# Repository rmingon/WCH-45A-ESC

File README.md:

# WCH-45A-ESC

An open-hardware 45A Electronic Speed Controller (ESC) project based on the WCH CH32M007 RISC-V microcontroller.

## Project Overview

This project aims to provide a robust and cost-effective ESC capable of handling continuous currents up to 45A. It utilizes the CH32M007G8R6, a RISC-V MCU specifically designed for motor control applications with integrated op-amps and comparators.

### Why Choose the CH32M007?

The **WCH CH32M007** stands out as a premier choice for modern **motor control applications**. Key advantages include:

- **Integrated Analog Peripherals:** With **3x built-in Op-Amps** and **4x Comparators**, the CH32M007 simplifies **current sensing** and **BEMF detection** layouts, reducing external component count and **BOM cost**.
- **High-Performance RISC-V Core:** The **144MHz QingKe V4F core** delivers the computational speed required for complex **FOC (Field Oriented Control)** loops and high-RPM management.
- **Dedicated Motor Control Logic:** Features advanced timers for complementary PWM generation with hardware dead-time, ensuring safe and efficient **MOSFET switching**.
- **Cost Efficiency:** It offers a highly competitive price point for **BLDC** and **PMSM** driver solutions without compromising on performance.

## Hardware Design

### MOSFET Selection

The power stage is the most critical aspect of this 45A design. We selected the **Alpha & Omega AON6500** N-Channel MOSFET for the following reasons:

1.  **Ultra-Low On-Resistance ($R_{DS(on)}$):** With a typical resistance of **~1.0 mΩ** (at $V_{GS}=10V$), conduction losses ($P = I^2 R$) are drastically reduced. This allows the ESC to handle 45A continuous current with minimal heat generation.
2.  **Thermal Management:** The **DFN5x6** package provides excellent thermal coupling to the PCB copper pours, eliminating the need for bulky external heatsinks in typical airflow conditions.
3.  **Voltage Rating ($V_{DS}$):** The **30V** breakdown voltage offers sufficient headroom for 2S-4S LiPo configurations, capable of withstanding inductive voltage spikes during switching.
4.  **Optimized Gate Charge:** The gate charge is balanced to allow for fast switching speeds (reducing switching losses) while remaining within the drive capability of the gate driver circuitry.

### CH32M007 KiCad Symbol

The custom KiCad schematic symbol and footprint for the **CH32M007G8R6** are included directly in this repository.

- **Location:** See the `root` repo.
- **Usage:** These libraries can be imported into KiCad to modify the design or create new derivatives.

## Firmware & Programming

The firmware source code is located in the `software` folder. The project is specifically configured for **MounRiver Studio 2**.

### How to Program

To flash the firmware onto the CH32M007, you will need a **WCH-LinkE** or compatible programmer.

1.  **Connections:**
    - Connect the **SWDIO**, **SWCLK**, **3V3**, and **GND** pads on the ESC to the WCH-Link.
2.  **Toolchain:**

    - The project is set up to use the `RISC-V Cross GCC` toolchain.
    - Build the project to generate the `.hex` or `.elf` file.

3.  **Flashing:**
    - Use **WCH-LinkUtility** or the built-in flasher in MounRiver Studio.
    - Select the CH32M007 series chip and download the firmware.

## License

This project is licensed under the **CERN Open Hardware Licence Version 2 - Strongly Reciprocal (CERN-OHL-S)**.

```text
CERN Open Hardware Licence Version 2 (Strongly Reciprocal) — CERN-OHL-S v2.0

You may obtain a copy of the license text from CERN:
https://ohwr.org/project/cernohl/wikis/Documents/CERN-OHL-version-2
```

If you redistribute this project (in source or manufactured form), you must comply with the terms of CERN-OHL-S v2.0.

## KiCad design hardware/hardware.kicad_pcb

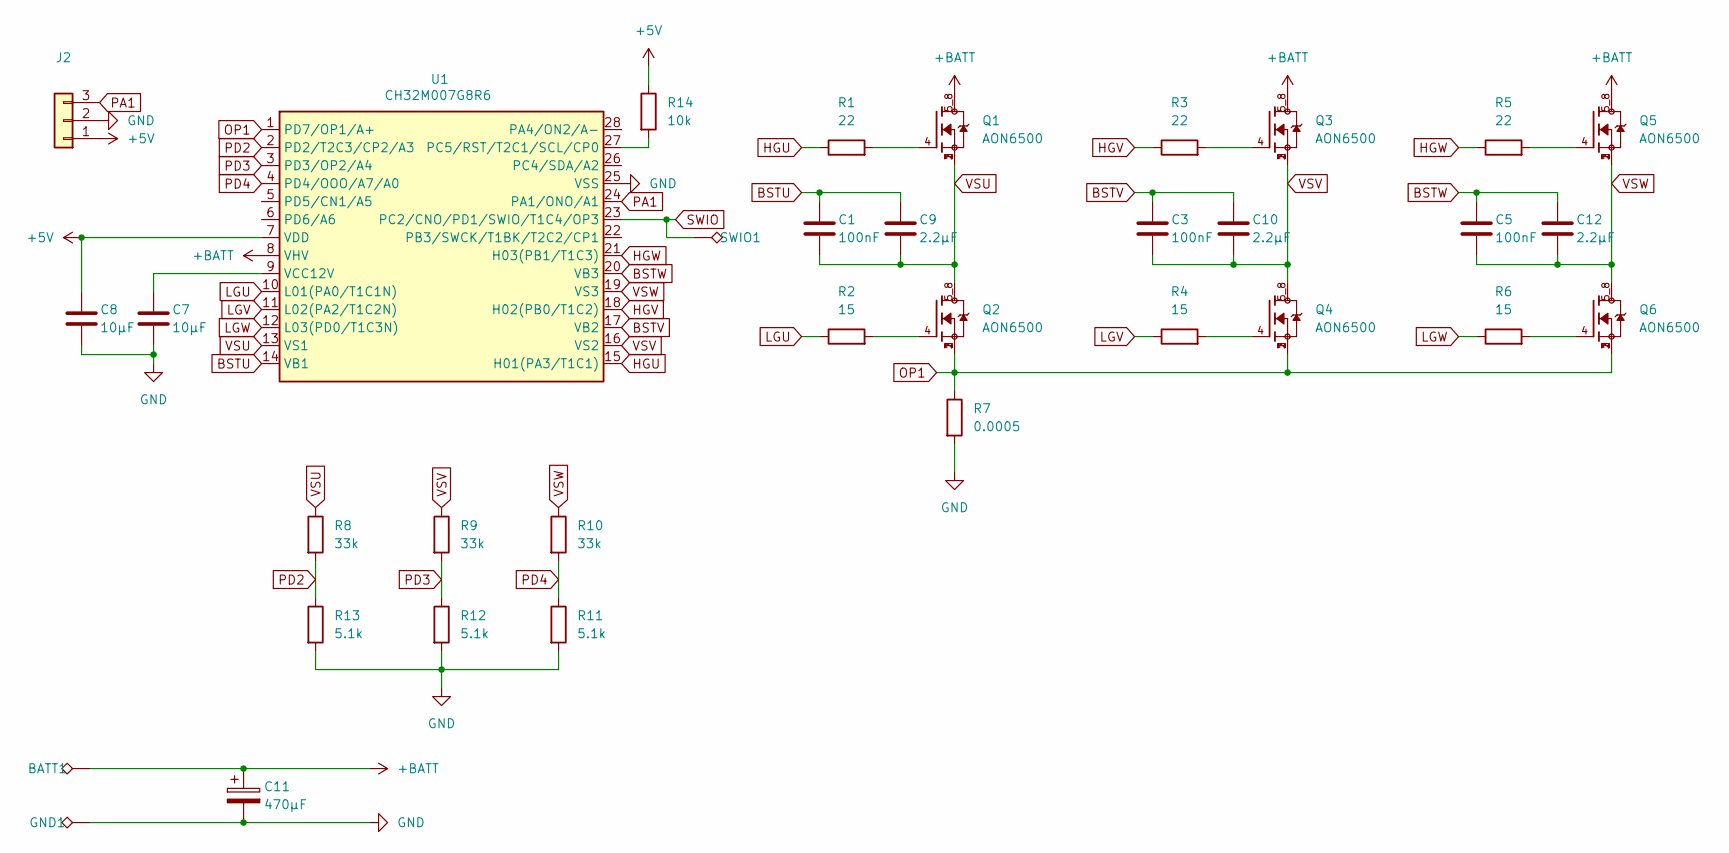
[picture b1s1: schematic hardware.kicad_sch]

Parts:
BATT1: TestPoint_Alt; TestPoint_Pad_3.0x3.0mm
C1, C3, C5: 100nF; C_1206_3216Metric
C7, C8: 10µF; C_1206_3216Metric
C9, C10, C12: 2.2µF; C_1206_3216Metric
C11: 470µF; CP_Radial_D10.0mm_P5.00mm
GND1: TestPoint_Alt; TestPoint_Pad_3.0x3.0mm
J2: Conn_01x03; PinHeader_1x03_P2.54mm_Vertical
Q1, Q2, Q3, Q4, Q5, Q6: AON6500; TRANS_AON6500; PARTREV F
R1, R3, R5: 22; R_0603_1608Metric
R2, R4, R6: 15; R_0603_1608Metric
R7: 0.0005; R_2512_6332Metric
R8, R9, R10: 33k; R_0603_1608Metric
R11, R12, R13: 5.1k; R_0603_1608Metric
R14: 10k; R_0603_1608Metric
SWIO1: TestPoint_Alt; TestPoint_Pad_1.5x1.5mm
U1: CH32M007G8R6; TSSOP-28_4.4x9.7mm_P0.65mm

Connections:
+5V: C8.2, J2.1, R14.1, U1.7 (VDD)
+BATT: BATT1.1 (1_1), C11.1, Q1.5_8, Q3.5_8, Q5.5_8, U1.8 (VHV)
BSTU: C1.1, C9.2, U1.14 (VB1)
BSTV: C3.1, C10.2, U1.17 (VB2)
BSTW: C5.1, C12.2, U1.20 (VB3)
GND: C7.1, C8.1, C11.2, GND1.1 (1_1), J2.2, R7.2, R11.2, R12.2, R13.2, U1.25 (VSS)
HGU: R1.1, U1.15 (H01(PA3/T1C1))
HGV: R3.1, U1.18 (H02(PB0/T1C2))
HGW: R5.1, U1.21 (H03(PB1/T1C3))
LGU: R2.1, U1.10 (L01(PA0/T1C1N))
LGV: R4.1, U1.11 (L02(PA2/T1C2N))
LGW: R6.1, U1.12 (L03(PD0/T1C3N))
unnamed: Q1.4, R1.2
unnamed: Q2.4, R2.2
unnamed: Q3.4, R3.2
unnamed: Q4.4, R4.2
unnamed: Q5.4, R5.2
unnamed: Q6.4, R6.2
unnamed: R14.2, U1.27 (PC5/RST/T2C1/SCL/CP0)
unnamed: C7.2, U1.9 (VCC12V)
OP1: Q2.1, Q2.2, Q2.3, Q4.1, Q4.2, Q4.3, Q6.1, Q6.2, Q6.3, R7.1, U1.1 (PD7/OP1/A+)
PA1: J2.3, U1.24 (PA1/ONO/A1)
PD2: R8.2, R13.1, U1.2 (PD2/T2C3/CP2/A3)
PD3: R9.2, R12.1, U1.3 (PD3/OP2/A4)
PD4: R10.2, R11.1, U1.4 (PD4/OOO/A7/A0)
SWIO: SWIO1.1 (1_1), U1.23 (PC2/CNO/PD1/SWIO/T1C4/OP3)
VSU: C1.2, C9.1, Q1.1, Q1.2, Q1.3, Q2.5_8, R8.1, U1.13 (VS1)
VSV: C3.2, C10.1, Q3.1, Q3.2, Q3.3, Q4.5_8, R9.1, U1.16 (VS2)
VSW: C5.2, C12.1, Q5.1, Q5.2, Q5.3, Q6.5_8, R10.1, U1.19 (VS3)

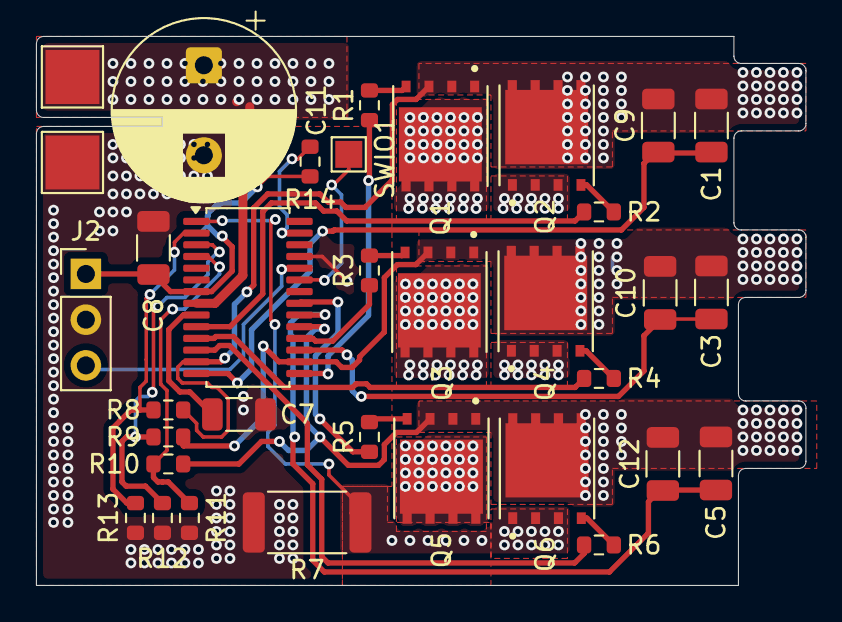
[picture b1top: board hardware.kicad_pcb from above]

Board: 2 copper layers, 42.8 x 30.5 mm, 34 parts (0 on the bottom side), 29 nets.

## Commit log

2026-01-10 add mosfet wiring
2026-01-11 add ch32m007 kicad symbol
2026-01-11 wire esc + add minimal connector for ch32m007
2026-01-11 wire bemf
2026-01-11 add pad gnd and wire drivers with pwm
2026-01-11 finish wire pcb
2026-01-11 add programming pad
2026-01-11 add pictures
2026-01-11 add license
2026-01-11 add 3.3v connection
2026-01-11 add software logic
2026-01-11 add readme
2026-05-02 add battery capacitor
2026-05-02 update capacitor
2026-05-02 change gate resistors
